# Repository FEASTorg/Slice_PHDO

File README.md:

# 1-Channel Atlas EZO Carrier (ACAR S2L)

A BREAD Slice that carries one Atlas Scientific EZO circuit on an Atlas
Electrically Isolated EZO Carrier Board Gen 2. Any EZO circuit the
carrier supports fits: pH, ORP, dissolved oxygen, conductivity, RTD
temperature and others. The carrier provides the galvanic isolation and
the probe's SMA connector.

Slice_ACAR_S2L is the small (S, 70 x 100 mm), 2-layer, one-channel
board, with the Nano at the fleet's standard position. The two-channel
board is Slice_ACAR_L2L (L format). Both grew out of the 2022 pH and
dissolved-oxygen board SLC_PHDO.

> **Status:** laid out, not built or tested (first revision, G3 r1).

## Fitting the carrier

The carrier lies flat on four standoffs over the top right of the
Slice (A2: four holes, no pads), turned so its SMA jack points toward
the front panel and down, toward the Nano's USB side. The carrier is
modified before it goes on:

1. **Take the kit header off.** Desolder the right-angle 1x05 header
   the carrier ships with.
2. **Fit a new header on the bottom.** Solder a stock 1x05 2.54 mm
   right-angle male header to the carrier's **bottom** side, in the
   same holes, pins pointing inward (toward the middle of the
   carrier), with its plastic about 1 mm off the board.
3. **Cut the rear socket tails.** Cut the three tails of the rear EZO
   socket row flush with the carrier's bottom (0.5 mm or less), so
   the cable housing passes under them.
4. **Use 6 mm standoffs** (#4-40 or M3), not the 11 mm ones in the
   Atlas kit; the cable runs under the carrier in that gap. On 6 mm
   the carrier with its EZO stands about 21.3 mm above the Slice
   (6 mm standoff, 1.6 mm carrier board, 8.7 mm EZO socket, 5.0 mm of
   EZO above the socket), against the 21.6 mm the slice case leaves
   above the board: about 0.3 mm to spare, so check on the first
   build that the lid closes; a taller lid is the fallback. On 11 mm
   it would stand about 26.3 mm.

The Slice keeps both copper layers 4 mm clear of each A2 hole centre,
so a #4-40 screw head (4.6 mm), a #4-40 or M3 nut, or a 1/4-in hex
standoff (corners at 3.67 mm) never touches its ground. The carrier's
datasheet (Atlas Scientific, Electrically Isolated EZO Carrier Board
Gen 2, V 1.6, pages 1-2) draws its four holes with plated rings, and
its schematic does not show which ground, isolated or not, those rings
join.

The Dupont housing on the new header then lies under the carrier, in
the 6 mm gap. The five wires turn toward the carrier's DC/DC
converter side, pass under the converter and rise to J3 beside the
carrier. The board keeps the space under the carrier free: no part
inside the carrier's outline, Slice parts at most 2.1 mm tall under the
housing and at most 1.8 mm under the wire path.

### The cable

J3 is a vertical 1x05 male header beside the carrier, its row turned
to the carrier's angle, in the carrier header's order: VCC, OFF, GND,
TX/SDA, RX/SCL (pin 1 nearest the board's top edge).

Requirement: a 5-wire female-female jumper, 2.54 mm Dupont housings,
26 AWG or finer, about 3 inches (75 mm) long. Candidate: Pololu's
3-inch premium F-F jumper wires, or their 10-wire ribbon cable
(item 4560) peeled down to 5 wires. The kit's own cable is not used.

### Probe plug and the front panel

The SMA jack and the mated probe plug stay inside the case, behind the
sliding front panel. The plug measured just over 20 mm long on the
author's probes; the fit allows 21 mm. The probe coax turns inside the
case on a radius of about 15 mm, a design assumption rather than a
datasheet figure (about 5 times the 2.8 mm outside diameter of
RG-174), and leaves through a notch in the front panel:

| Notch | Slot frame | Board frame (x from the bus edge, y from the top edge) |
| --- | --- | --- |
| centre | A -32.7 | y 82.7, at the front edge (x 70) |
| width | 5.5 mm along A | y 79.95 to 85.45 |
| height | open bottom to N 9.0 | about 10.3 mm above the top copper |

The slice case does not cut this notch yet. Its tooling
(bread-mechanical `slice-case/design/synth/tools/resolve.py`) makes a
front-panel notch only for a top-side part whose courtyard crosses the
board's front edge; this board has none (the jack and plug stay
inside), and there is no enclosure modifier for a panel notch (the
modifiers are `wall_notches`, `floor_reliefs` and `roof_windows`, for
the tray). The front-zone constraints, and a way for a board to declare
a cable notch, are pending
[bread-infra#43](https://github.com/feastorg/bread-infra/issues/43).
Until then, cut the notch above in a stock panel by hand.

## Modes

A slide switch (SW1) with two positions sets both the carrier's supply
and where its two data lines go. Each end of SW1 is marked on the silk;
the slider joins both commons to the two pins at one end.

| SW1 end (silk) | Carrier supply | Carrier TX/SDA, RX/SCL go to | Who talks to the EZO |
| --- | --- | --- | --- |
| `3V3 I2C`, direct (pads 1, 6) | 3.3 V | the slot bus SDA and SCL | the host (Loaf controller), over I2C |
| `5V UART`, proxy (pads 3, 4) | 5 V | the Nano's UART pins | the Nano, over UART |

The carrier pulls its data lines up to its own supply through 4.7 kOhm. A
carrier on the slot bus therefore always runs at 3.3 V, so it never pulls
a 3.3 V host's SDA and SCL up toward 5 V. A pull-up on the switch's control
line selects the UART side if the switch is between positions, which keeps
a carrier off the slot bus.

Direct mode needs no Slice firmware: the host reads the EZO at its own I2C
address. Proxy mode needs Nano firmware that relays EZO traffic; it does
not exist yet.

### Changing the mode

1. On the bench, set the EZO's protocol: `I2C,n` for direct mode, or
   `Baud,n` for proxy mode (Atlas EZO datasheets).
2. Power the Slice off.
3. Move SW1 to the end marked for the mode. On a new board, check it
   once with a meter before a carrier goes on: J3 pin 1 reads 3.3 V
   with SW1 at the `3V3 I2C` end and 5 V at the `5V UART` end.

An EZO left in UART mode on the slot bus drives SDA from its TX line and
can hang the bus.

A direct-mode carrier adds its 4.7 kOhm pull-ups to the host's own.
Keep to at most two direct-mode carriers on one bus, across all
Slices.

## Pin map (Arduino Nano)

| Nano pin | Net | Use |
| --- | --- | --- |
| D2 | E_STOP | slot bus |
| D3 | INT | slot bus |
| D4 | SYNC | slot bus |
| A4 / A5 | I2C_DAT / I2C_CLK | slot bus I2C |
| D5 | CH1_OFF | carrier OFF |
| D7 | CH1_TX | Nano TX to carrier RX (proxy) |
| D8 | CH1_RX | carrier TX to Nano RX (proxy) |
| D12 | LED | WS2812 status LED |

D5, D7 and D8 keep the 2022 board's channel-1 pins; D6, D9 and D10
(its channel 2) are free here and carry channel 2 on Slice_ACAR_L2L.
The status LED, on D5 in the Slice template, moves to D12.

OFF has no pull-up on this board; the carrier pulls it up itself. Drive it
open-drain: output LOW turns the carrier and its EZO off, input (high
impedance) turns them on. Do not drive it high: a 5 V high would reach a
3.3 V carrier in direct mode.

## Power

- U1 (AP63205) makes +5V from the bus +12V: the Nano, the LED, the carrier in
  proxy mode and U2.
- U2 (AP7361C-33E LDO) makes +3V3 from +5V: the carrier in direct mode
  and the Qwiic jack (J1).

Per the Atlas carrier datasheet, a carrier with an EZO draws 53 to 82 mA
at 5 V and 84 to 97 mA at 3.3 V, depending on the circuit.

## Provenance

The circuit is re-entered from **SLC_PHDO R0 2022**, the BREAD pH and
dissolved-oxygen carrier published on OSF:
[osf.io/zbg98](https://osf.io/zbg98/). That board had two carrier sockets
with I2C/UART jumpers and ran both carriers from 5 V. This revision keeps
its socket order and Nano pins and adds the switched supply, the 3.3 V
rail, local decoupling and the G3 S-format Nano template, r2 (12 V buck,
slot bus links, option-B Nano supply, mounting).

## Documentation

Please refer to the [docs](/docs) for more info.

---

<div align="center">
  
</div>

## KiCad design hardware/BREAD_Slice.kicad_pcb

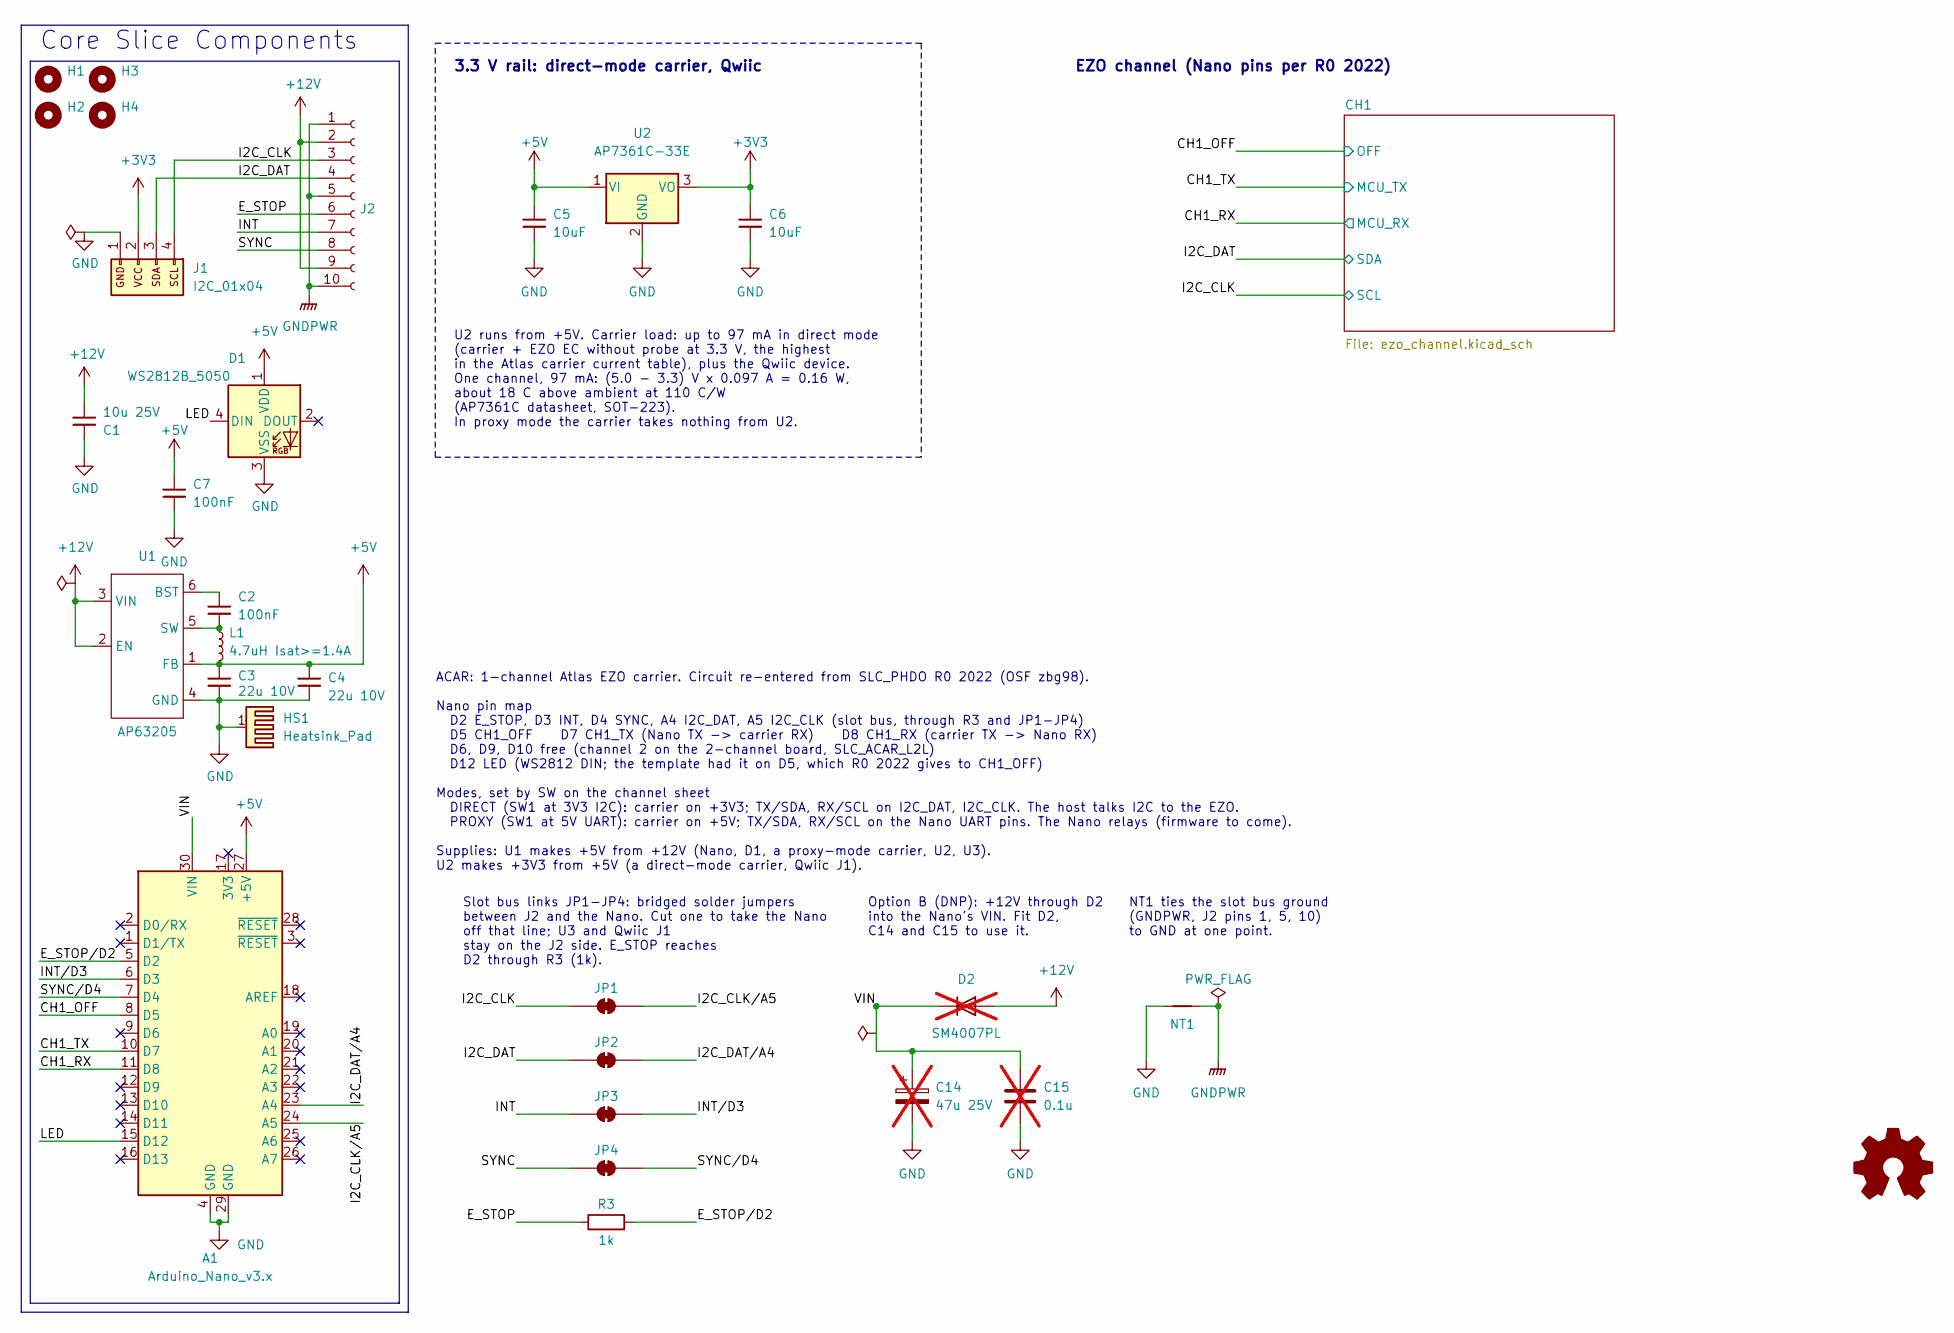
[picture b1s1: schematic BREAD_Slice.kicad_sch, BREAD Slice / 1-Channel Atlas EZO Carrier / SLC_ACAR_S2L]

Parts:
A1: Arduino_Nano_v3.x; Arduino_Nano_Headers
C1: 10u 25V; C_1206_3216Metric
C2: 100nF; C_1206_3216Metric
C3, C4: 22u 10V; C_1206_3216Metric
C5, C6: 10uF; C_0805_2012Metric
C7: 100nF; C_0805_2012Metric
C14: 47u 25V; CP_Elec_6.3x7.7; not fitted
C15: 0.1u; C_0805_2012Metric_Pad1.18x1.45mm_HandSolder; not fitted
D1: WS2812B_5050; WS2812-5050-4PIN
D2: SM4007PL; D_SOD-123F; not fitted
H1, H2, H3, H4: MountingHole; MountingHole_5mm
HS1: Heatsink_Pad; Thermal_Pad
J1: I2C_01x04; JST_SH_SM04B-SRSS-TB_1x04-1MP_P1.00mm_Horizontal
J2: Conn_01x10_Female; PinSocket_1x10_P2.54mm_Horizontal
JP1: I2C_CLK bus link; SolderJumper-2_P1.3mm_Bridged_RoundedPad1.0x1.5mm
JP2: I2C_DAT bus link; SolderJumper-2_P1.3mm_Bridged_RoundedPad1.0x1.5mm
JP3: INT bus link; SolderJumper-2_P1.3mm_Bridged_RoundedPad1.0x1.5mm
JP4: SYNC bus link; SolderJumper-2_P1.3mm_Bridged_RoundedPad1.0x1.5mm
L1: 4.7uH Isat>=1.4A; L_1210_3225Metric
NT1: NetTie_2; NetTie-2_SMD_Pad2.0mm
R3: 1k; R_0603_1608Metric
U1: AP63205; SOIC_05WU-7_DIO
U2: AP7361C-33E; SOT-223-3_TabPin2

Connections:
+3V3: C6.1, J1.2, U2.3 (VO); also elsewhere on the board
+5V: A1.27 (+5V), C3.2, C4.2, C5.1, C7.1, D1.1 (VDD), L1.2, U1.1 (FB), U2.1 (VI); also elsewhere on the board
+12V: C1.2, D2.2 (A), J2.2, J2.9, U1.2 (EN), U1.3 (VIN)
/CH1_OFF: A1.8 (D5); also elsewhere on the board
/CH1_RX: A1.11 (D8); also elsewhere on the board
/CH1_TX: A1.10 (D7); also elsewhere on the board
/E_STOP: J2.6, R3.1
/E_STOP/D2: A1.5 (D2), R3.2
/I2C_CLK: J1.4, J2.3, JP1.1 (A); also elsewhere on the board
/I2C_CLK/A5: A1.24 (A5), JP1.2 (B)
/I2C_DAT: J1.3, J2.4, JP2.1 (A); also elsewhere on the board
/I2C_DAT/A4: A1.23 (A4), JP2.2 (B)
/INT: J2.7, JP3.1 (A)
/INT/D3: A1.6 (D3), JP3.2 (B)
/LED: A1.15 (D12), D1.4 (DIN)
/SYNC: J2.8, JP4.1 (A)
/SYNC/D4: A1.7 (D4), JP4.2 (B)
/VIN: A1.30 (VIN), C14.1, C15.1, D2.1 (K)
GND: A1.4 (GND), A1.29 (GND), C1.1, C3.1, C4.1, C5.2, C6.2, C7.2, C14.2, C15.2, D1.3 (VSS), HS1.1, J1.1, NT1.1, U1.4 (GND), U2.2 (GND); also elsewhere on the board
GNDPWR: J2.1, J2.5, J2.10, NT1.2
unnamed: C2.2, U1.6 (BST)
unnamed: C2.1, L1.1, U1.5 (SW)

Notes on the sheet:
EZO channel (Nano pins per R0 2022)
3.3 V rail: direct-mode carrier, Qwiic
ACAR: 1-channel Atlas EZO carrier. Circuit re-entered from SLC_PHDO R0 2022 (OSF zbg98). Nano pin map D2 E_STOP, D3 INT, D4 SYNC, A4 I2C_DAT, A5 I2C_CLK (slot bus, through R3 and JP1-JP4) D5 CH1_OFF D7 CH1_TX (Nano TX -> carrier RX) D8 CH1_RX (carrier TX -> Nano RX) D6, D9, D10 free (channel 2 on t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
Core Slice Components
U2 runs from +5V. Carrier load: up to 97 mA in direct mode (carrier + EZO EC without probe at 3.3 V, the highest in the Atlas carrier current table), plus the Qwiic device. One channel, 97 mA: (5.0 - 3.3) V x 0.097 A = 0.16 W, about 18 C above ambient at 110 C/W (AP7361C datasheet, SOT-223). In pro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
Slot bus links JP1-JP4: bridged solder jumpers between J2 and the Nano. Cut one to take the Nano off that line; U3 and Qwiic J1 stay on the J2 side. E_STOP reaches D2 through R3 (1k).
Option B (DNP): +12V through D2 into the Nano's VIN. Fit D2, C14 and C15 to use it.
NT1 ties the slot bus ground (GNDPWR, J2 pins 1, 5, 10) to GND at one point.

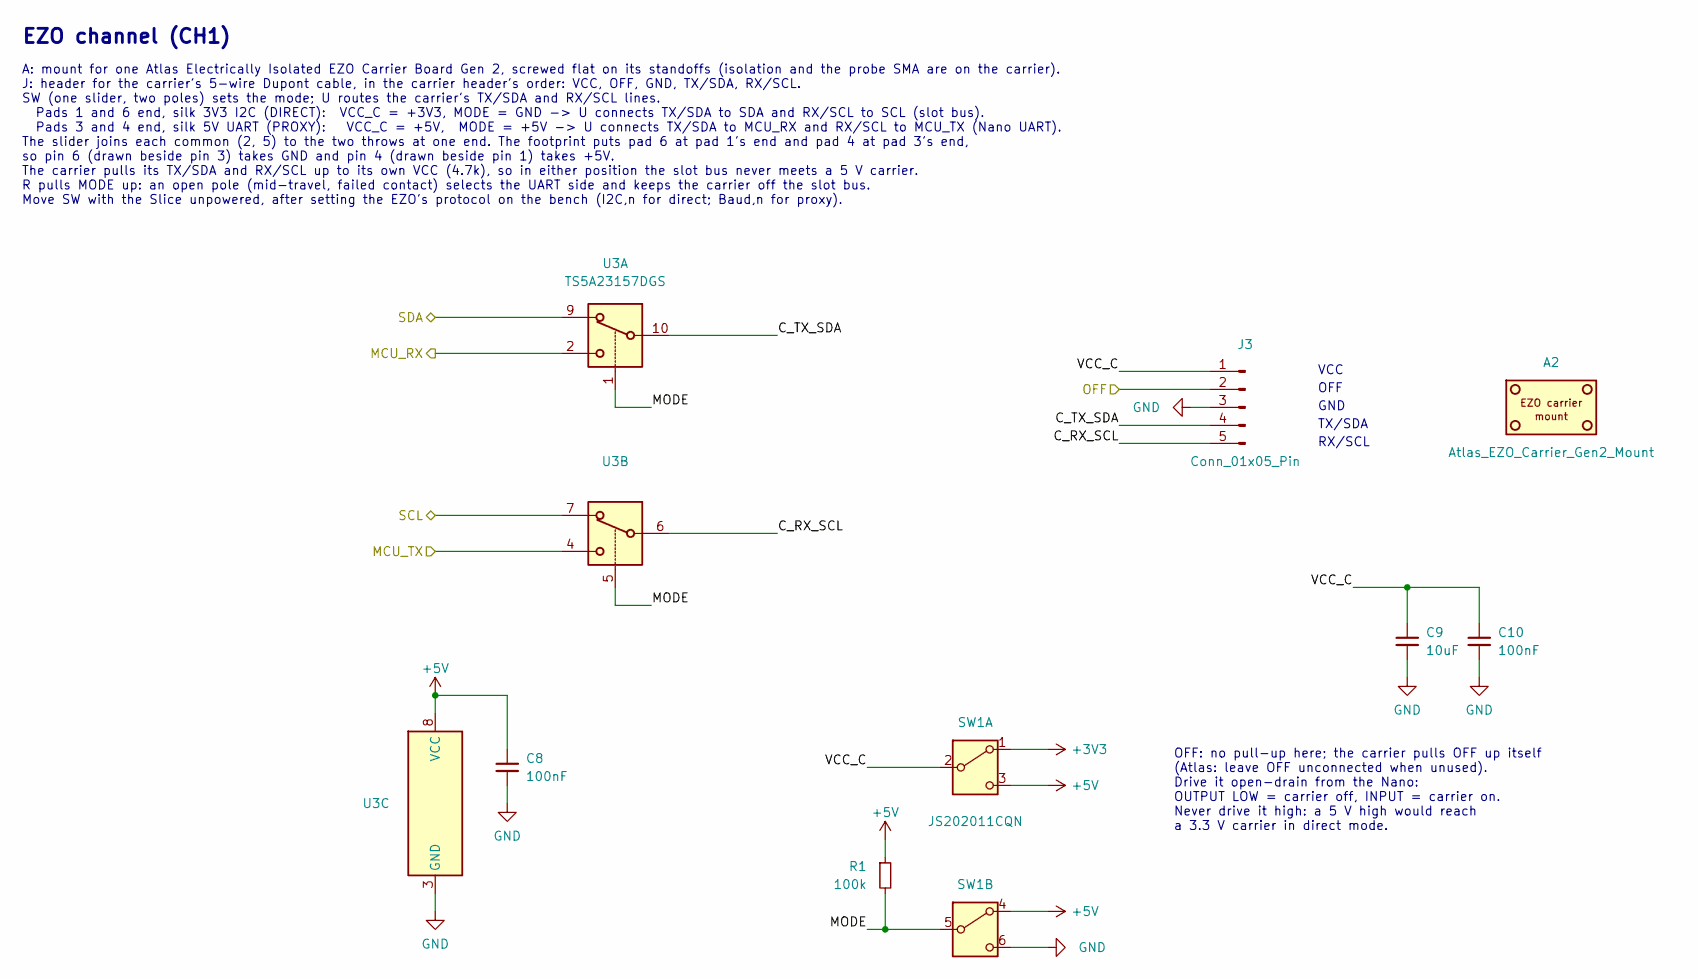
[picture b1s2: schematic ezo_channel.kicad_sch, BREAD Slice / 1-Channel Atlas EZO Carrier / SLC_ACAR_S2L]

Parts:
A2: Atlas_EZO_Carrier_Gen2_Mount
C8, C10: 100nF; C_0805_2012Metric
C9: 10uF; C_0805_2012Metric
J3: Conn_01x05_Pin; PinHeader_1x05_P2.54mm_Vertical
R1: 100k; R_0805_2012Metric
SW1: JS202011CQN; SW_CK_JS202011CQN_DPDT_Straight
U3: TS5A23157DGS; TSSOP-10_3x3mm_P0.5mm

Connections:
+3V3: SW1.1 (A); also elsewhere on the board
+5V: C8.1, R1.1, SW1.3 (C), SW1.4 (A), U3.8 (VCC); also elsewhere on the board
/CH1/C_RX_SCL: J3.5, U3.6
/CH1/C_TX_SDA: J3.4, U3.10
/CH1/MODE: R1.2, SW1.5 (B), U3.1, U3.5
/CH1/VCC_C: C9.1, C10.1, J3.1, SW1.2 (B)
/CH1_OFF: J3.2; also elsewhere on the board
/CH1_RX: U3.2; also elsewhere on the board
/CH1_TX: U3.4; also elsewhere on the board
/I2C_CLK: U3.7; also elsewhere on the board
/I2C_DAT: U3.9; also elsewhere on the board
GND: C8.2, C9.2, C10.2, J3.3, SW1.6 (C), U3.3 (GND); also elsewhere on the board

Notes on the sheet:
VCC
A: mount for one Atlas Electrically Isolated EZO Carrier Board Gen 2, screwed flat on its standoffs (isolation and the probe SMA are on the carrier). J: header for the carrier's 5-wire Dupont cable, in the carrier header's order: VCC, OFF, GND, TX/SDA, RX/SCL. SW (one slider, two poles) sets the mo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
EZO channel (CH1)
OFF: no pull-up here; the carrier pulls OFF up itself (Atlas: leave OFF unconnected when unused). Drive it open-drain from the Nano: OUTPUT LOW = carrier off, INPUT = carrier on. Never drive it high: a 5 V high would reach a 3.3 V carrier in direct mode.
OFF
RX/SCL
TX/SDA
GND

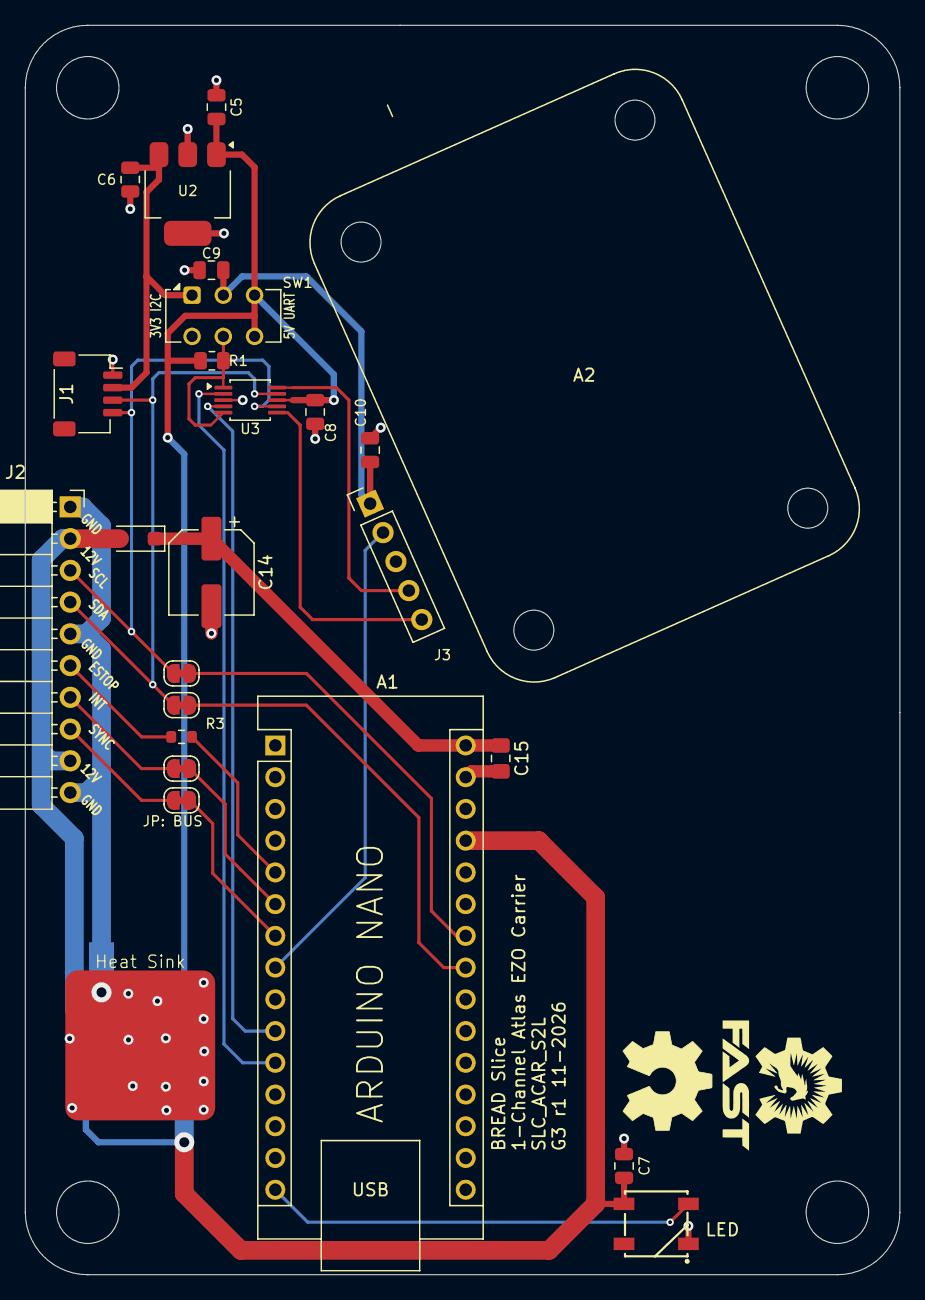
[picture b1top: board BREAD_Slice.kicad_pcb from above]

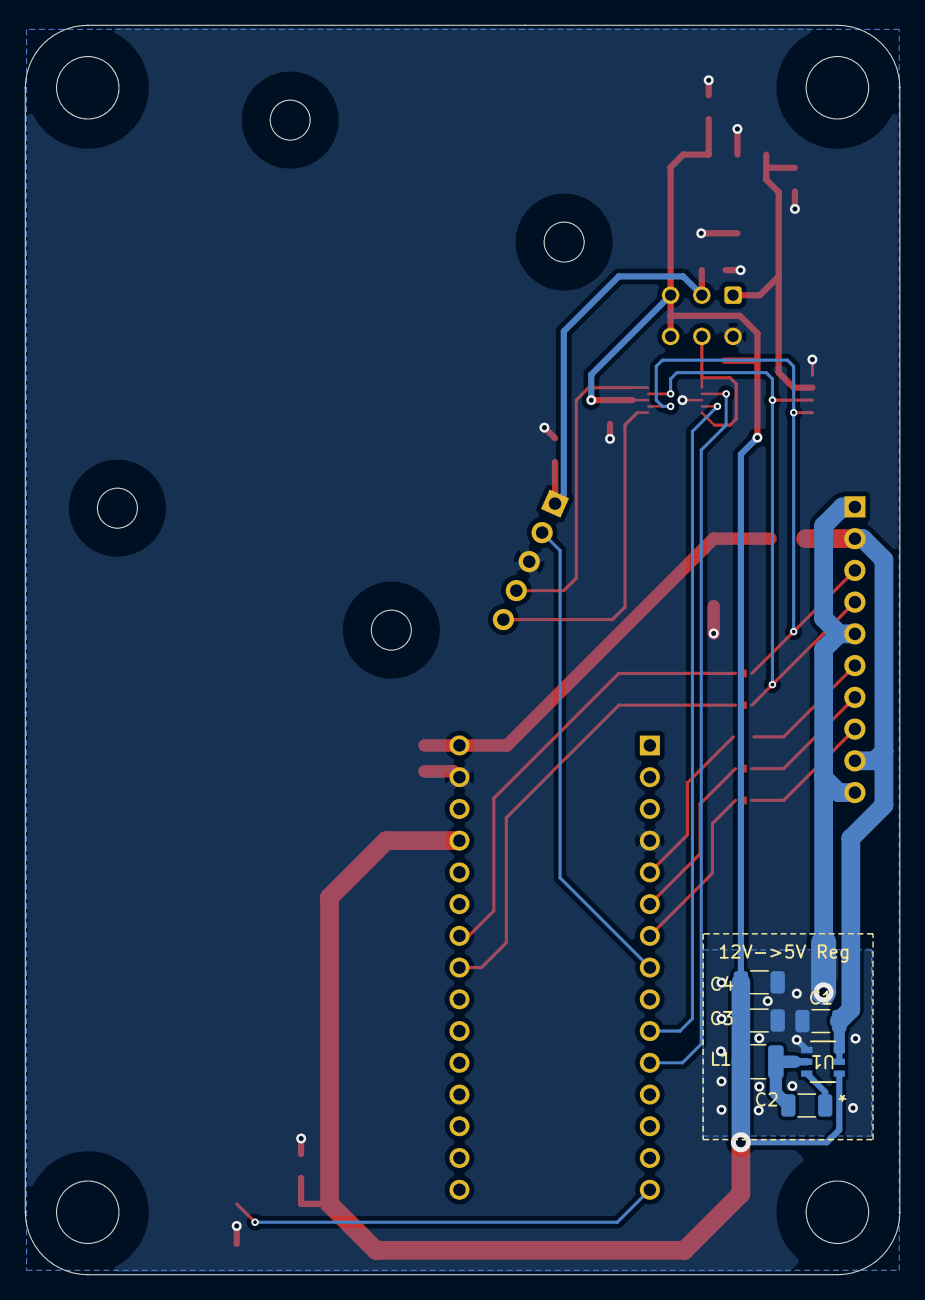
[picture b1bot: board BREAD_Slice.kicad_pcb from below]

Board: 2 copper layers, 70.0 x 100.0 mm, 38 parts (7 on the bottom side), 26 nets.

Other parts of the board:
LOGO1: Val**; OSHW_Logo_8mm
LOGO2: LOGO; FAST-Logo-Medium

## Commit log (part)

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2026-05-20 Add slice.yaml manifest (schema v1.0)
2026-05-24 Add KiBot/docs pipeline
2026-05-24 Update TODO with CI findings
2026-05-24 Standardize TODO.md with Pass 1/Pass 2 structure
